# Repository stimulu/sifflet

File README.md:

# sifflet
Design files for sifflet

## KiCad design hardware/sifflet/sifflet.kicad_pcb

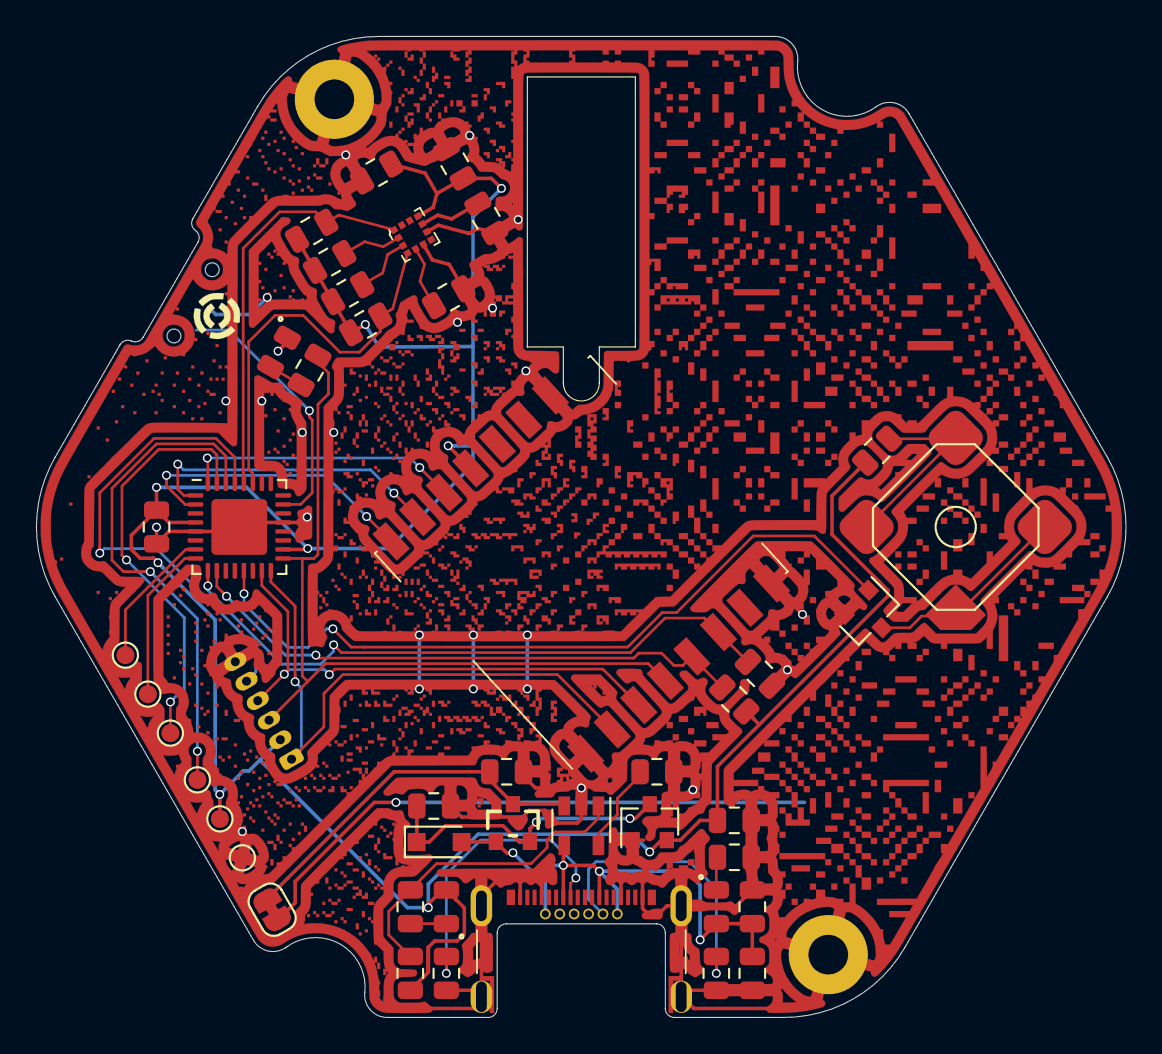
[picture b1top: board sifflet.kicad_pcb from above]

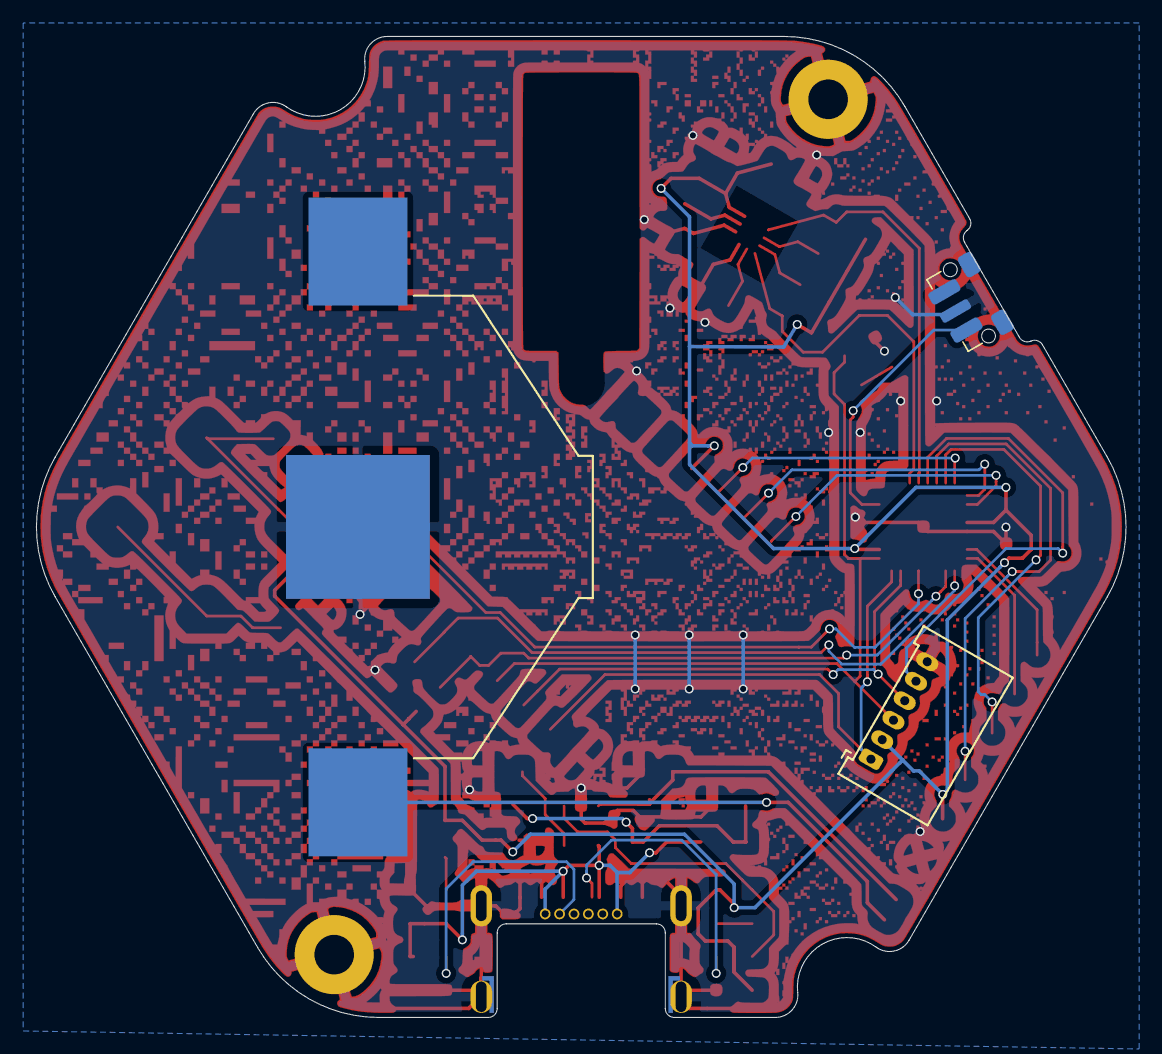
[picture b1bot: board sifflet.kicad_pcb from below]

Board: 2 copper layers, 60.5 x 54.5 mm, 49 parts (3 on the bottom side), 35 nets.

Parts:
BT1: Battery LIR2450; BatteryHolder_Keystone_3008_1x2450
BZ1: Buzzer; KSSG74B16_BUZZER
C1, C2, C4: 0.1µF; C_0805_2012Metric
C3: 0.1µf; C_0805_2012Metric
C5: 10µF; C_0805_2012Metric
C6, C7, C8: 4.7µF; C_0805_2012Metric
C9: 1µF; C_0805_2012Metric
D1: ON; LED_0805_2012Metric
D2: LED_CTRL; LED_0805_2012Metric
D3: CHARGING; LED_0805_2012Metric
D4: BAT60JFILM; D_SOD-323_HandSoldering
H1, H2: MountingHole_Pad; MountingHole_2.2mm_M2_Pad
J1: CX70M-24P1; USB-C_Female_CX70M-24P1
J2: ICSP header; Molex_PicoBlade_53048-0610_1x06_P1.25mm_Horizontal
JP1: Current test point; SolderJumper-2_P1.3mm_Bridged_RoundedPad1.0x1.5mm
Q1: BSS138; SOT-23
Q2: DMP1045U; SOT23_FET
R1, R2: 5K1 PULLDOWN; R_0805_2012Metric
R3, R9: 470; R_0805_2012Metric
R4: 1K I2C PULLUP; R_0805_2012Metric
R5, R6: 10K CS_PULLUP; R_0805_2012Metric
R7: 1K; R_0805_2012Metric
R8: 1K1 I2C PULLUP; R_0805_2012Metric
R10, R11: 10K; R_0805_2012Metric
R12: R_Small; R_0805_2012Metric
R13: 10K CALIB CHRG; R_0805_2012Metric
R14: 100K CHRG INIT LOAD; R_0805_2012Metric
R15: 47K PULLUP 3V; R_0805_2012Metric
SW1: SW_Push; TL3340_SWITCH_SMD
TP1: GND; TestPoint_Pad_D1.0mm
TP2: VCC; TestPoint_Pad_D1.0mm
TP3: RX; TestPoint_Pad_D1.0mm
TP4: XTAL1; TestPoint_Pad_D1.0mm
TP5: TX; TestPoint_Pad_D1.0mm
TP6: XTAL2; TestPoint_Pad_D1.0mm
U1: ATmega328PB-MU; QFN-32-1EP_5x5mm_P0.5mm_EP3.1x3.1mm
U2: LSM303C; LGA-12_9x9mm_LSM303C
U3: RFM95W-868S2; HOPERF_RFM9XW_SMD
U4: MCP73831-2-OT; SOT-23-5
U5: MCP1700-3302E_SOT23; SOT-23

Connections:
/A0: SW1.1, U1.23
/A4: R4.2, U1.27, U2.4
/A5: R8.2, U1.28, U2.1
/Digital_0: TP3.1, U1.30
/Digital_1: TP5.1, U1.31
/Digital_2: U1.32, U3.14
/Digital_3: U1.1, U3.15
/Digital_4: U1.2, U3.16
/Digital_5: R11.2, U1.9, U3.6
/Digital_6: R10.1, U1.10, U3.5
/Digital_9: Q1.1, U1.13
/Digital_11: J2.4, U1.15, U3.3
/Digital_12: J2.1, U1.16, U3.2
/Digital_13: J2.3, R7.2, U1.17, U3.4
/Digital_20: TP4.1, U1.7
/Digital_21: TP6.1, U1.8
/RST: J2.5, U1.29
/STAT: R9.2, R15.2, U4.1
/V_LIPO: BT1.1, JP1.1
/V_USB: C6.1, D1.2, D4.2, J1.A4, J1.A9, J1.B4, J1.B9, Q2.2, R14.1, U4.4
/sheet5CF66014/V_UNREG: C8.1, D4.1, Q2.3, U5.3
GND: BT1.2, C1.1, C2.2, C3.2, C4.2, C5.2, C6.2, C7.2, C8.2, C9.2, D2.1, H1.1, H2.1, J1.A1, J1.A12, J1.B1, J1.B12, J1.SH, J2.6, Q1.2, R1.2, R2.2, R3.2, R11.1, R13.2, R14.2, SW1.2, TP1.1, U1.5, U1.21, U1.33, U2.6, U2.8, U3.1, U3.8, U3.10, U4.2, U5.1
unnamed: BZ1.1, R12.2
unnamed: BZ1.2, Q1.3
unnamed: C2.1, U2.5
unnamed: C7.1, JP1.2, Q2.1, U4.3
unnamed: D1.1, R3.1
unnamed: D2.2, R7.1
unnamed: D3.1, R9.1
unnamed: J1.A5, R2.1
unnamed: J1.B5, R1.1
unnamed: R5.2, U2.2
unnamed: R6.1, U2.3
unnamed: R13.1, U4.5
VCC: C1.2, C3.1, C4.1, C5.1, C9.1, D3.2, J2.2, R4.1, R5.1, R6.2, R8.1, R10.2, R12.1, R15.1, TP2.1, U1.4, U1.18, U2.9, U2.10, U3.13, U5.2

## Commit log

2019-03-28 Add directories
2019-05-08 Setup hardware files
2019-05-13 Add Gerbers extensions to gitignore
2019-05-13 PCB mechanical validation
2019-12-20 CHanges for july 2019
2019-12-20 remove local references
2019-12-20 Added contour file
2019-12-20 correct file for pcb edges added
